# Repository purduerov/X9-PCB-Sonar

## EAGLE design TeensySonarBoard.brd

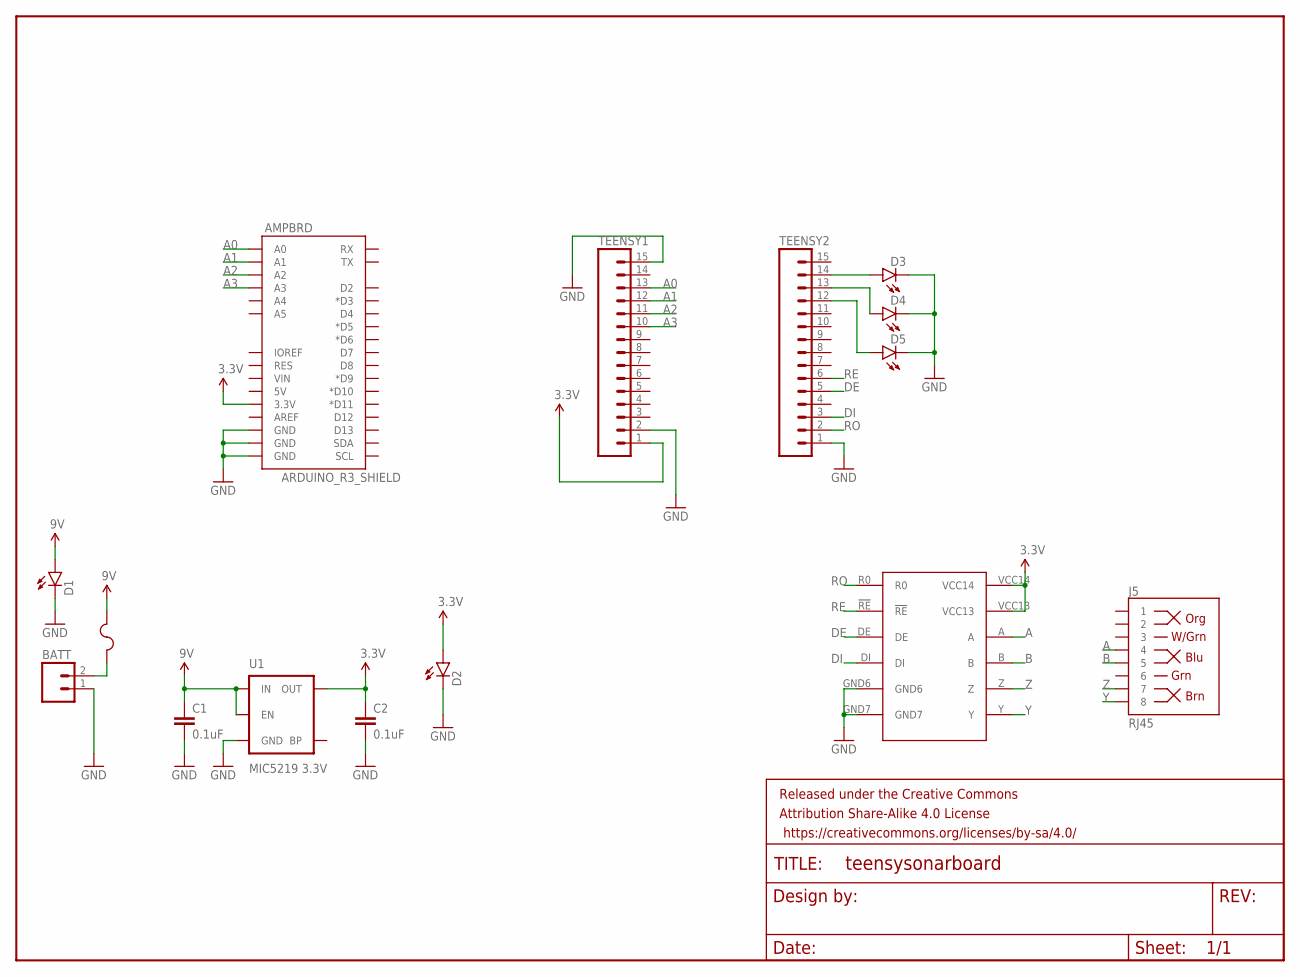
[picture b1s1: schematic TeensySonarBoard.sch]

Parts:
AMPBRD: ARDUINO_R3_SHIELD; UNO_R3_SHIELD
BATT: M02JST-PTH-VERT; JST-2-PTH-VERT
C1, C2: 0.1uF; 0603-CAP
D1, D2, D3, D4, D5: LED0603; LED-0603
F1: 2A; KEYSTONE_FUSE_3587
FRAME1: FRAME-LETTERNO_PACKAGE; DUMMY
J5: RJ45; RJ45-8
TEENSY1, TEENSY2: M15; 1X15
U1: MIC5219 3.3V; SOT23-5
U$1: MAX3491

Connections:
3.3V: AMPBRD.3.3V, C2.1, D2.A, TEENSY1.1, U1.5 (OUT), U$1.VCC13, U$1.VCC14
A: J5.4, U$1.A
A0: AMPBRD.A0, TEENSY1.13
A1: AMPBRD.A1, TEENSY1.12
A2: AMPBRD.A2, TEENSY1.11
A3: AMPBRD.A3, TEENSY1.10
B: J5.5, U$1.B
DE: TEENSY2.5, U$1.DE
DI: TEENSY2.3, U$1.DI
GND: AMPBRD.GND@0 (GND), AMPBRD.GND@1 (GND), AMPBRD.GND@2 (GND), BATT.1, C1.2, C2.2, D1.C, D2.C, D3.C, D4.C, D5.C, TEENSY1.2, TEENSY1.15, TEENSY2.1, U1.2 (GND), U$1.GND6, U$1.GND7
unnamed: BATT.2, F1.P$1, F1.P$2
unnamed: D3.A, TEENSY2.14
unnamed: D4.A, TEENSY2.13
unnamed: D5.A, TEENSY2.12
RE: TEENSY2.6, U$1.!RE
RO: TEENSY2.2, U$1.R0
VCC: C1.1, D1.A, F1.P$3, F1.P$4, U1.1 (IN), U1.3 (EN)
Y: J5.8, U$1.Y
Z: J5.7, U$1.Z

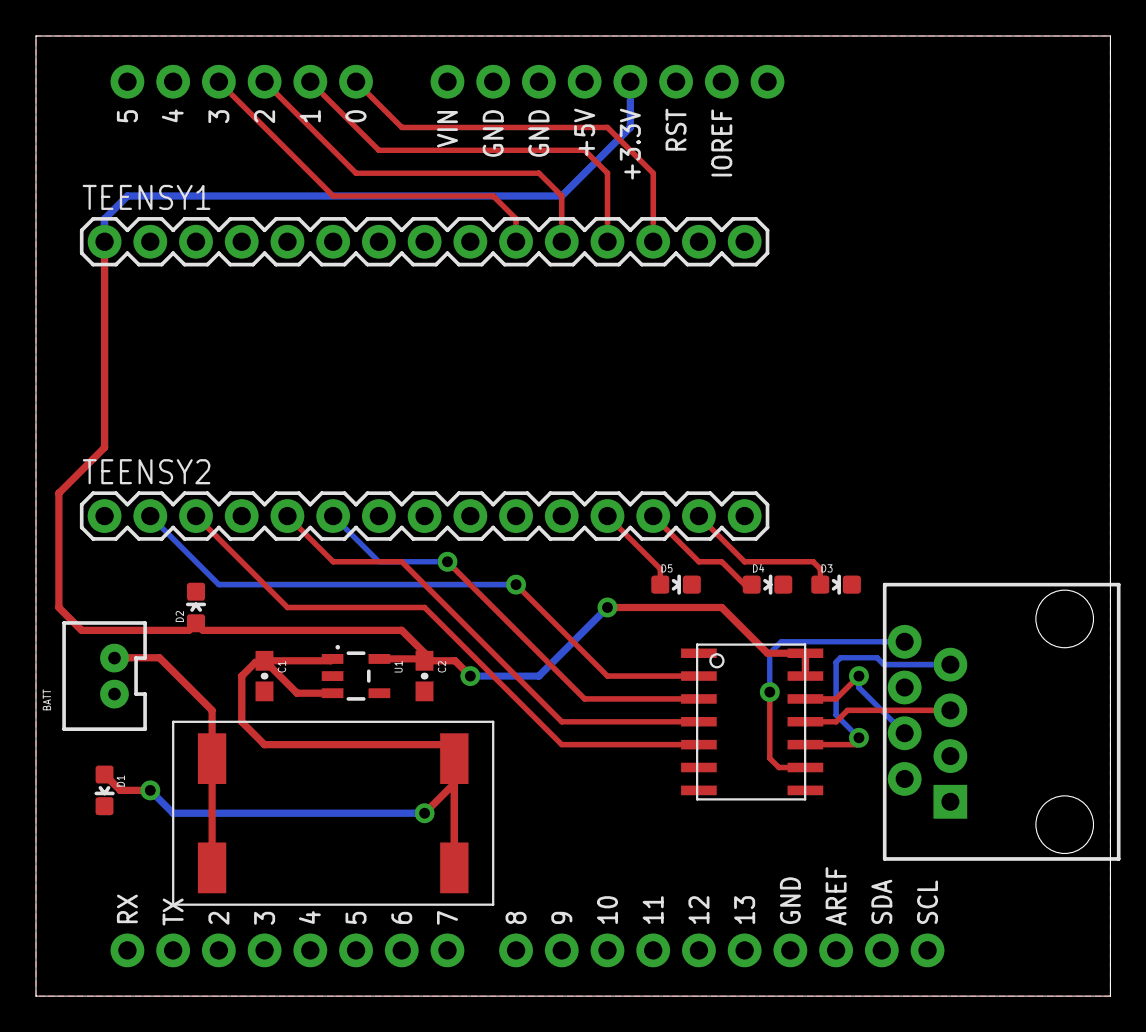
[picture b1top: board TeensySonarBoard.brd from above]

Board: 2 copper layers, 59.7 x 53.3 mm, 16 parts (0 on the bottom side), 19 nets.

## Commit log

2016-10-22 Sonar Board from X-8
2016-11-02 OutputJob
2016-11-30 Added teensy sonar board files.
2016-11-30 Forgot to add files to commit, actually added teensy board files now.
2016-12-06 Changed design rules to gold pheonix.
2016-12-07 Added a 2A fuse to the board to meet MATE requirements.
2017-01-03 Corrected DRC errors by updating RS485 chip from parts library.
2017-01-04 Initial placement of diagnostic LEDs.
2017-01-04 Placed LEDs onto board.
2017-01-14 Added BOM html file
2017-01-26 fixed ledissues

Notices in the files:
parts and their libraries:
SparkFun-Connectors: Licensing: Creative Commons ShareAlike 4.0 International - https://creativecommons.org/licenses/by-sa/4.0
SparkFun-Aesthetics: Released under the Creative Commons Attribution Share-Alike 4.0 License
SparkFun-Aesthetics: https://creativecommons.org/licenses/by-sa/4.0
